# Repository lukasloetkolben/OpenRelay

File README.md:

# Open Source Relay for Openpilot

**_Note:_**  the device has been tested and works perfectly!

If you have any questions contact me on Discord: loetkolben#2962

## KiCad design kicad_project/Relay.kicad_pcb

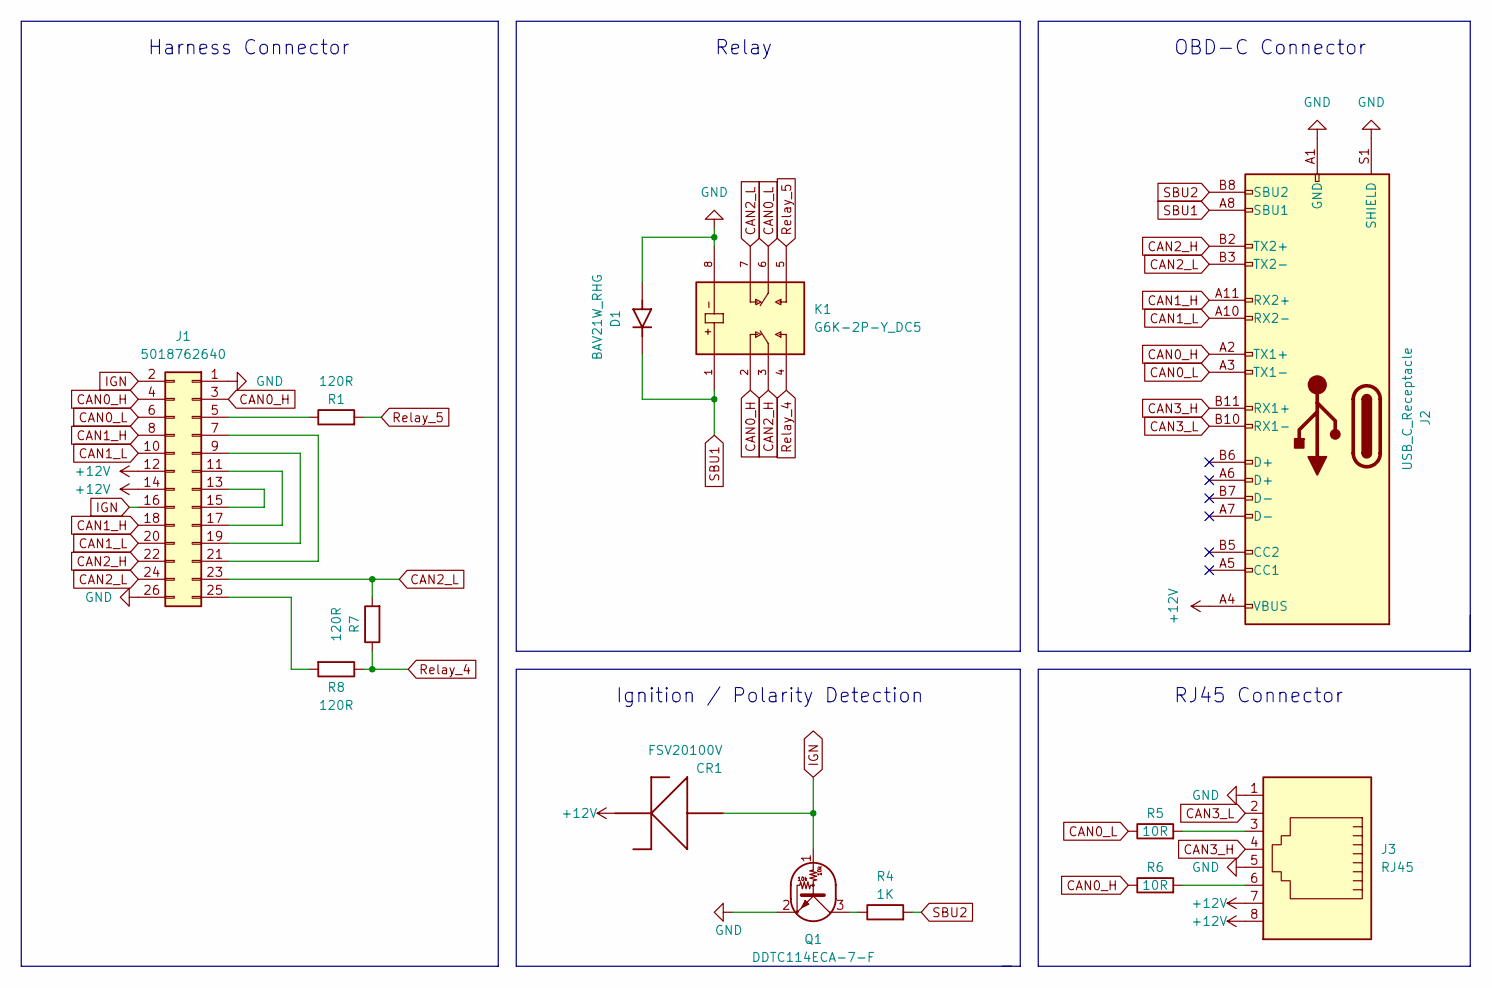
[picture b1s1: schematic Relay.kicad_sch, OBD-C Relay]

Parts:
CR1: FSV20100V; TO-277; PARTNO FSV20100VCT-ND
D1: BAV21W_RHG; DIO_BAV21W_RHG; PARTREV K1804
J1: 5018762640; JST_PHD_B26B-PHDSS_2x13_P2.00mm_Vertical
J2: USB_C_Receptacle; TYPE-C-31-M-04
J3: RJ45; RJ45_Amphenol_54602-x08_Horizontal
K1: G6K-2P-Y_DC5; RELAY_G6K-2P-Y_DC3; PARTREV K106-E1-11
Q1: DDTC114ECA-7-F; SOT-23
R1, R7, R8: 120R; R_2010_5025Metric_Pad1.40x2.65mm_HandSolder
R4: 1K; R_2010_5025Metric_Pad1.40x2.65mm_HandSolder
R5, R6: 10R; R_0603_1608Metric

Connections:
+12V: CR1.3, J1.12, J1.14, J2.A4 (VBUS), J2.A9 (VBUS), J2.B4 (VBUS), J2.B9 (VBUS), J3.7, J3.8
CAN0_H: J1.3, J1.4, J2.A2 (TX1+), K1.2, R6.1
CAN0_L: J1.6, J2.A3 (TX1-), K1.6, R5.1
CAN1_H: J1.8, J1.18, J2.A11 (RX2+)
CAN1_L: J1.10, J1.20, J2.A10 (RX2-)
CAN2_H: J1.22, J2.B2 (TX2+), K1.3
CAN2_L: J1.23, J1.24, J2.B3 (TX2-), K1.7, R7.2
CAN3_H: J2.B11 (RX1+), J3.4
CAN3_L: J2.B10 (RX1-), J3.2
GND: D1.A, J1.1, J1.26, J2.31, J2.32, J2.33, J2.34, J2.A1 (GND), J2.A12 (GND), J2.B1 (GND), J2.B12 (GND), J2.S1 (SHIELD), J3.1, J3.5, K1.8, Q1.2 (E)
IGN: CR1.1, CR1.2, J1.2, J1.16, Q1.1 (B)
unnamed: J1.5, R1.1
unnamed: J1.11, J1.17
unnamed: J1.13, J1.15
unnamed: J1.9, J1.19
unnamed: J1.7, J1.21
unnamed: J1.25, R8.2
unnamed: J3.3, R5.2
unnamed: J3.6, R6.2
unnamed: Q1.3 (C), R4.1
Relay_4: K1.4, R7.1, R8.1
Relay_5: K1.5, R1.2
SBU1: D1.C, J2.A8 (SBU1), K1.1
SBU2: J2.B8 (SBU2), R4.2

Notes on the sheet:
Harness Connector
Ignition / Polarity Detection
OBD-C Connector
RJ45 Connector
Relay

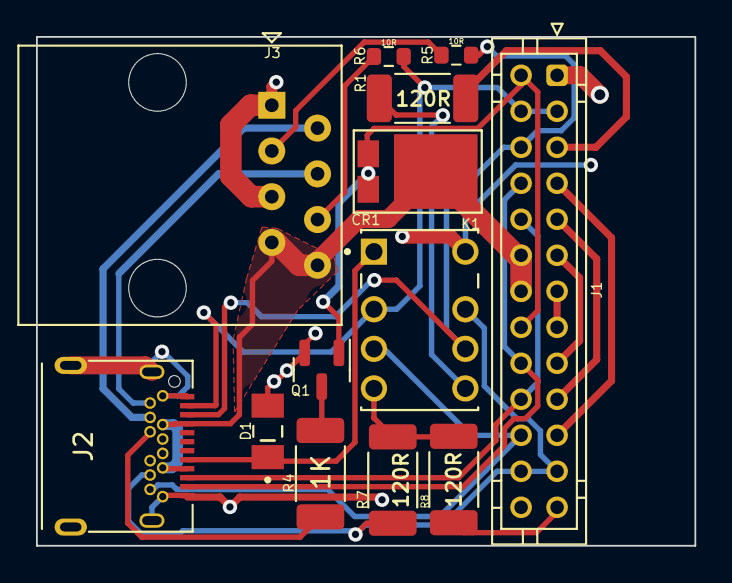
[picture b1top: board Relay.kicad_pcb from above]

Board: 2 copper layers, 36.6 x 28.3 mm, 13 parts (0 on the bottom side), 24 nets.

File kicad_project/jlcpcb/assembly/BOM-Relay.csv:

Comment,Designator,Footprint,LCSC
USB_C_Receptacle,J2,TYPE-C-31-M-04,C129018
10R,"R5,R6",R_0603_1608Metric,C22859
DDTC114ECA-7-F ,Q1,SOT-23,C260852
BAV21W_RHG,D1,DIO_BAV21W_RHG,
120R,R8,R_2010_5025Metric_Pad1.40x2.65mm_HandSolder,
120R,R7,R_2010_5025Metric_Pad1.40x2.65mm_HandSolder,
RJ45,J3,RJ45_Amphenol_54602-x08_Horizontal,
FSV20100V,CR1,TO-277,
5018762640,J1,JST_PHD_B26B-PHDSS_2x13_P2.00mm_Vertical,
1K,R4,R_2010_5025Metric_Pad1.40x2.65mm_HandSolder,
G6K-2P-Y_DC5,K1,RELAY_G6K-2P-Y_DC3,
120R,R1,R_2010_5025Metric_Pad1.40x2.65mm_HandSolder,

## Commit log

2022-05-26 Init
2022-05-26 BOM and OSHW Logo
2022-05-27 Create LICENSE
2022-05-27 added two more 12V vias
2022-05-27 thicker ignition line
2022-05-28 5V Relay not 3V
2022-05-28 gitignore
2022-05-28 README.md
2022-05-28 symbol SO2222 updated Symbol
2022-05-30 Warning
2022-06-06 new NPN Transistor
2022-06-11 back to SO2222 NPN Transistor
2022-06-12 finally fixed Transistor Issue. credits to mlocoteta
2022-06-12 schematics improvements. credits to mlocoteta
2022-06-15 tested
2022-06-27 update usb-c and pcb
2022-06-27 harness box
2023-03-18 updated BOM file for JLC
